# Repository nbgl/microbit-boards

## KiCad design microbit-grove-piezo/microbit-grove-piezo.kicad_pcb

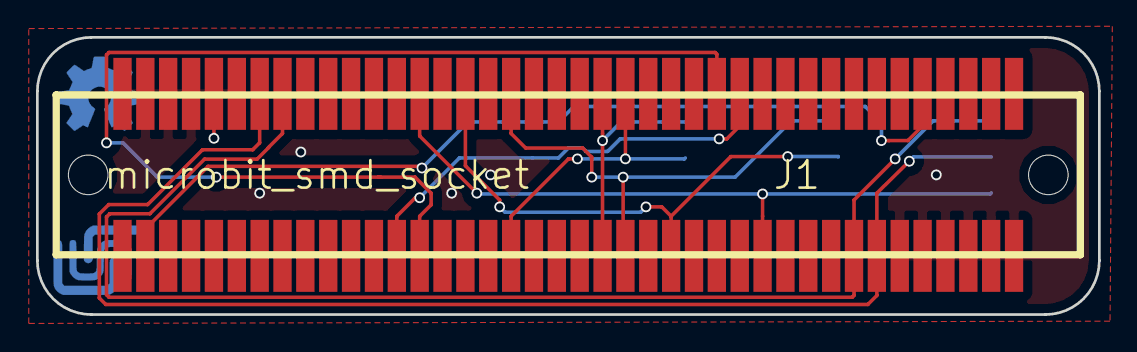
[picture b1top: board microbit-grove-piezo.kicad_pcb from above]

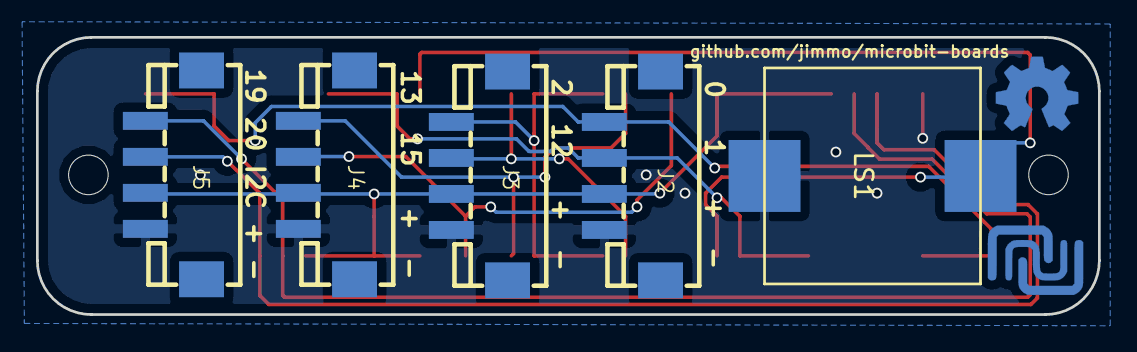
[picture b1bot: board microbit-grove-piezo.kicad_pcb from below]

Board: 2 copper layers, 59.0 x 15.4 mm, 8 parts (7 on the bottom side), 11 nets.

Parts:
J1: microbit_smd_socket; smd_socket
J2, J3, J4, J5: GROVE-CONNECTOR-SMD_4+2P-2.0_; HW4-SMD-2.0
LS1: Speaker; PKLCS1212E4001-R1
Z1: ncss; ncss_small
Z2: oshw; OSHW-Logo2_7.3x6mm_Copper_NoText

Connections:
MB_0: J1.1, J1.26, J2.1
MB_1: J1.2, J1.27, J2.2
MB_2: J1.3, J1.28, J3.1
MB_3V3: J1.20, J1.21, J1.22, J1.45, J1.46, J1.47, J2.3, J3.3, J4.3, J5.3
MB_8: J1.9, J1.34, LS1.1
MB_12: J1.13, J1.38, J3.2
MB_13: J1.14, J1.39, J4.1
MB_15: J1.16, J1.41, J4.2
MB_19: J1.18, J1.43, J5.1
MB_20: J1.19, J1.44, J5.2
MB_GND: J1.23, J1.24, J1.25, J1.48, J1.49, J1.50, J2.4, J3.4, J4.4, J5.4, LS1.2

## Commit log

2019-01-30 Change pinout
